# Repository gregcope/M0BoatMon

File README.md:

ABoatMon
========

A Moteino M0 (hence the M0) Boat Monitoring solution!

Intro
=====

A reimplementation, and extension of https://github.com/gregcope/piboatmon, as the original consumed too much power.  This is designed with the following goals;
* Be very, very low power
* Chargable from 12-24V 
* Has a rechargable LIPO battery

The present version is made from COTS parts to make life easy at the deign/proto stage.  However the code should be transferable.

Parts
=====
* [Adafruit Ultimate GPS](https://www.adafruit.com/product/746) - any 3.3v UART GPS would do, however needs an enable pin and vbat GPS almanac backup
* [Adafruit Fona](https://www.adafruit.com/product/1946) - any 3.3v UART GSM modem would do, although we do use the battery charging on the fona
* [Low power Moteino M0](https://lowpowerlab.com/shop/product/184) 
* [Mini Step Down Regulator Voltag Power Supply Module 4.5v~55v to 5v](https://www.ebay.co.uk/sch/i.html?_osacat=0&_odkw=Mini+Step+Down+Regulator+Voltag+Power+Supply+Module+4.5v~55v+to+5v&_from=R40&_trksid=p2334524.m570.l1313.TR0.TRC0.H0.XMini+Step+Down+Regulator+Voltag+Power+Supply+Module+4.5v~55v+to+5v+600ma.TRS0&_nkw=Mini+Step+Down+Regulator+Voltag+Power+Supply+Module+4.5v~55v+to+5v+600ma&_sacat=0).  Specifically the one with an enable pin and low power in off mode (<10ua).  Needs to supply 500ma+ (600ma is fine) and deal with 11-30v on the input to work on 12V or 24V systems.  Needs to supply 5V for the lipo charger.  Efficiency is not a massive issue as the regulator is off most of the time, only on to charge occassionally.
* [DS18B20 Waterproof Digital Probe Temperature Sensor with Silicone Cable (higher temp) Thermometer](https://www.ebay.co.uk/sch/i.html?_from=R40&_trksid=p2380057.m570.l1313.TR0.TRC0.H0.Xvermont+l+tent.TRS0&_nkw=DS18B20+Waterproof+Digital+Probe+Temperature+Sensor+Silicone+Cable+Thermometer&_sacat=0)
* [12V 12mm LED Power Push Button Switch Momentary Waterproof Metal 4 Pin](https://www.ebay.co.uk/sch/i.html?_osacat=0&_odkw=waterproof+LED+switch+12mm&_from=R40&_trksid=p2334524.m570.l1313.TR0.TRC0.H0.Xwaterproof+LED+switch+12mm+momentary.TRS0&_nkw=waterproof+LED+switch+12mm+momentary&_sacat=0)
* 1200mah LIPO Battery (any single cell LIPO with a JST would do)
* Bilge Switch (any normally closed, simple switch would do)

External Libs
=======

* [Tinygps++](https://github.com/mikalhart/TinyGPSPlus) - A class to deal with GPS
* [Lowpower](https://github.com/LowPowerLab/LowPower) - A class to help with Sleep modes
* Eeprom - Save Eeprom state
* [OneWire](https://github.com/PaulStoffregen/OneWire) - DS18B20 Temp sensor lib

Internal Classes
========
* Device - A base, or standlone class to control power to devices via a Digital pin
* Config - A class to provide a config object to store Eeprom state
* CRC8 - CRC checksum (for config saving)
* Sleep - Simple wrapper to LowPower sleep

High Level Logic
================

* Switches is on setup configures all the required parts
* Loop every 8 secs and checks;
* Bilge switch
* Every 4 mins checks the batteries
* and if above 13.7v (ie charging) enables the onboard lipo charger
* Reports bilge switch or low BatV
* Every Hour;
* Checkst the above
* Checks location
* If any of the above are out of band;
* Send a message

HowTo
=====

1. Open a command terminal, and change cd to where your Ardunio IDE stores code
```cd Documents/Arduino```
2. Clone the repo
```git clone https://github.com/gregcope/ABoatMon.git```
3. Open Ardunio IDE and open ```ABoatMon.ino```

http://arduino.stackexchange.com/questions/348/how-to-organize-my-arduino-projects-structure-for-easy-source-control

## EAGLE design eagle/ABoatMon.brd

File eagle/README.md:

# Eagle Files

0. Uses Sparkfun DRC file
1. ERC and DRC check clean
2. Top and bottom Copper Pour
3. Nets Classes use 24 mil width and 16mil clearance
4. Polygons use Isolate 12 mil
5. Layer 26 bNames - bottom silkscreen has board dimensions on it

## Design

0. I may add more parts...
1. Uses a MoteinoMega, Adafruit Ultimate GPS and an Adafruit FONA GSM
2. The P-channel Mosfet is designed to power the GPS directly, avoiding the on board regulator
3. The VBAT is on the MotinoMega 3.3V rail to keep the GPS backup circuits powered
4. The JST is for a Lipo battery
5. Their is a 1.8M/3.3M VCC voltage divider to monitor the LIPO, with a 0.1uF capacitor - see [Jeelabs post here](https://jeelabs.org/2013/05/16/measuring-the-battery-without-draining-it/)
6. Terminal Connector is for a simple Bilge switch for the Moteino to monitor
7. Terminal Connector for a Button
8. Terminal Connector for an LED
9. Terminal Connector for a DS18B20 Temp probe powered from a GPIO pin
10. Terminal Connector 12V-24V VCC input
11. A 27M/3.3M voltage divider to measure 30+V on an ADC pin
12. Headers for Fona GSM module
13. Terminal Connector for a 5v cable to connect to the Fona USB charge port
14. There is a jumper to measure the uCurrent the board uses from the LIPO, and also by-pass the switching (aka an on/off switch)
15. There is a jumper to measure the uCurrent the board uses from VCC, and also by-pass the switching (aka an on/off switch)
16. Voltage regulator uses a [holtek HT7463A](http://www.holtek.com/documents/10179/116711/HT7463A_Bv130.pdf)

... What's missing?

No thread is complete without pictures...

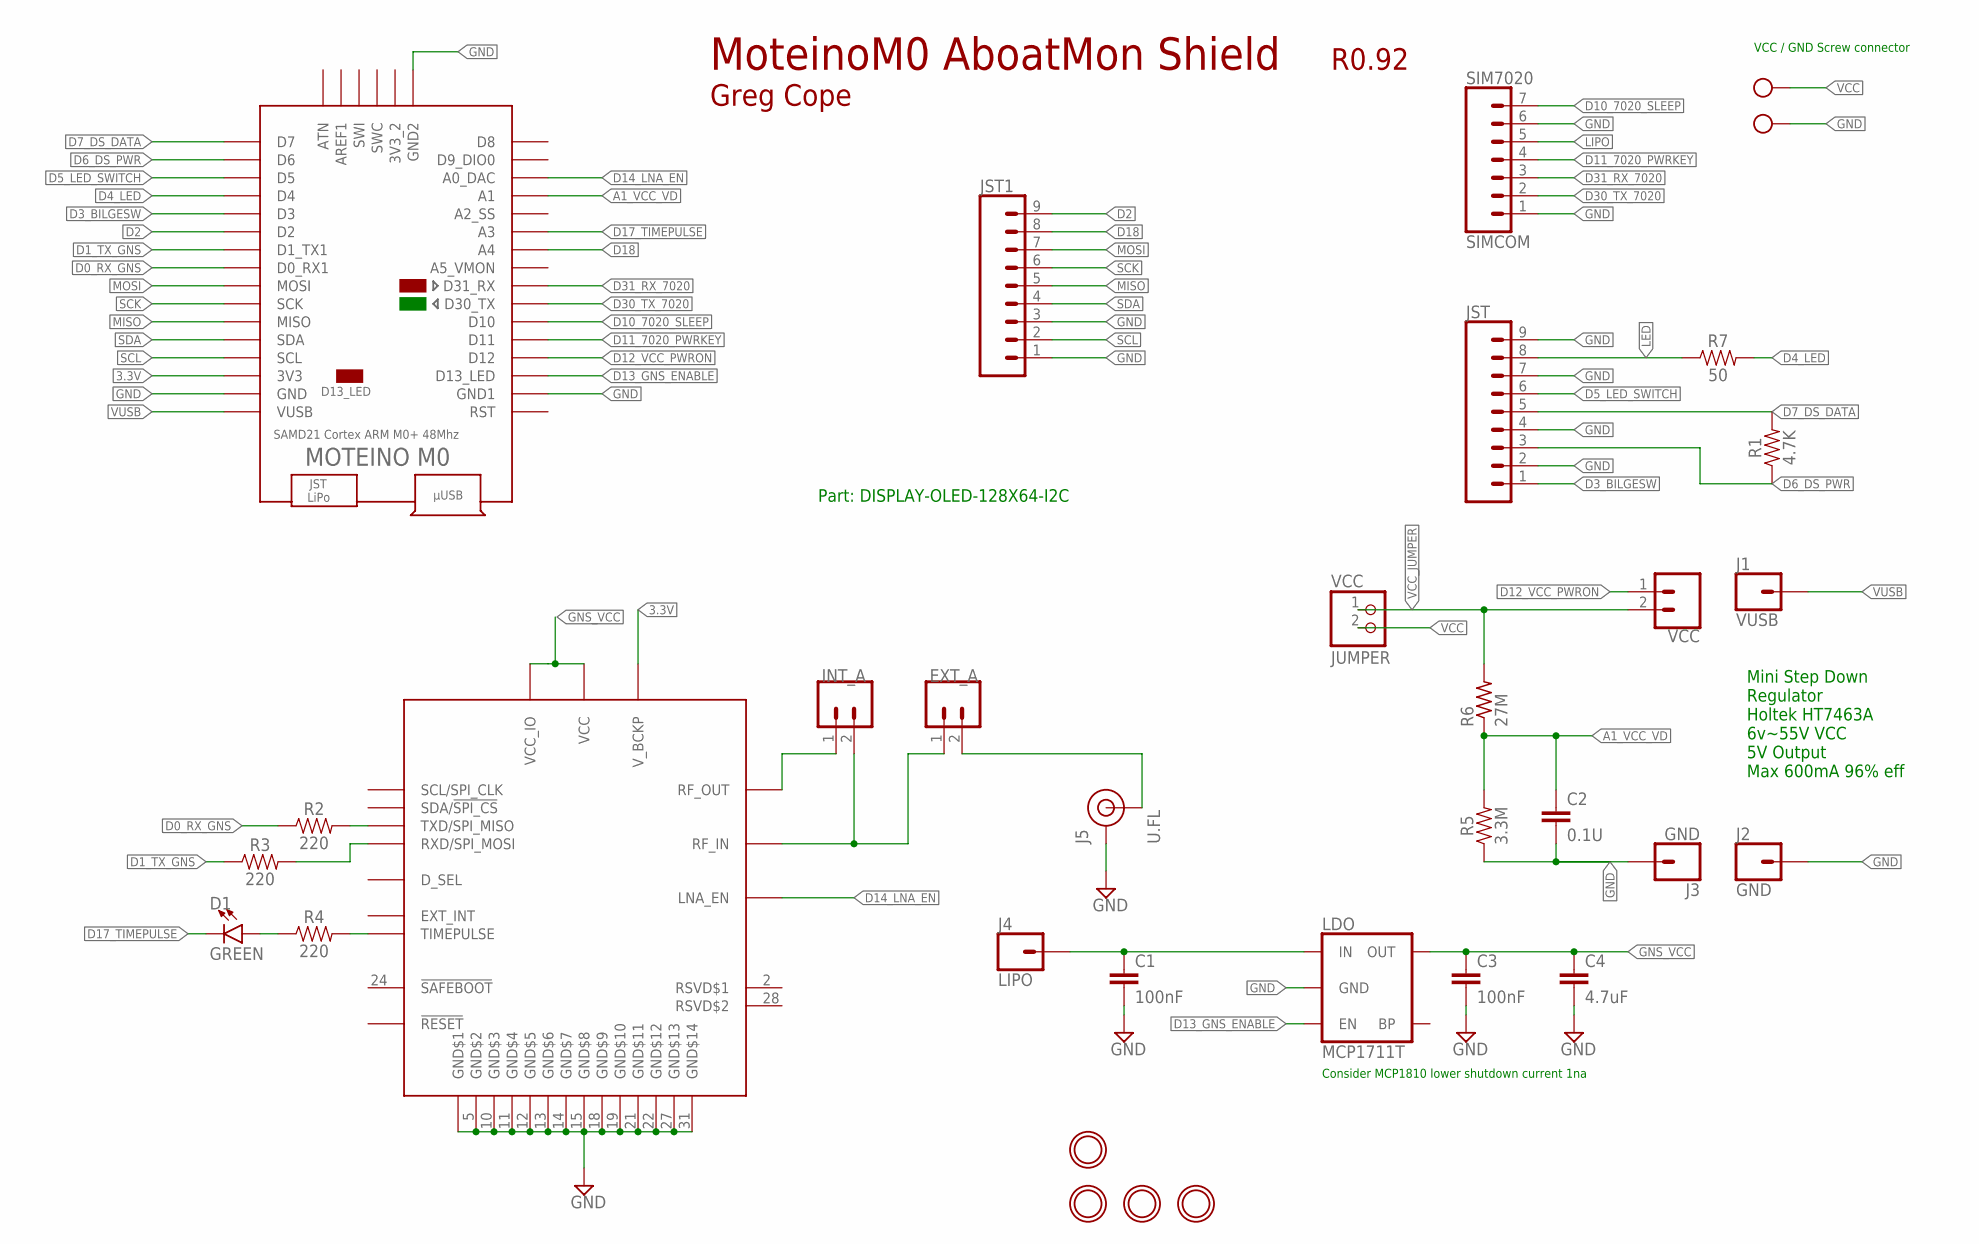
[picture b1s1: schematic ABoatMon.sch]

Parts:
C1, C3: 100nF; 0603
C2: 0.1U; CAP-PTH-SMALL-KIT
C4: 4.7uF; 0603
D1: GREEN; LED-0603
ENABLE: VCC; 1X02
EXT_A: CONN_02; 1X02
GND: MOUNTINGHOLE2.5; MOUNTINGHOLE_2.5_PLATED
INT_A: CONN_02; 1X02
J1: VUSB; 1X01
J2, J3: GND; 1X01
J4: LIPO; 1X01
J5: U.FL
JST, JST1: CONN_09; 1X09
LDO: MCP1711T; SOT23-5
R1: 4.7K; AXIAL-0.3
R2, R3, R4: 220; 0603
R5: 3.3M; AXIAL-0.3
R6: 27M; 0309/12
R7: 50; AXIAL-0.3
SIM7020: SIMCOM; 1X07
U$3, U$9: MOUNTINGHOLE2.0; MOUNTINGHOLE_2.0_PLATED
U$5: CAM-M8
U$6: MOTEINO_M0
U$7: MOUNTINGHOLE2.5; MOUNTINGHOLE_2.5_PLATED
VCC: JUMPER; 1X02_ROUND
X1: MKDSN1,5/2-5,08

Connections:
3.3V: U$5.8 (V_BCKP), U$6.3V3
A1_VCC_VD: C2.1, R5.P$2 (2), R6.1, U$6.A1
D0_RX_GNS: R2.1, U$6.D0_RX1
D1_TX_GNS: R3.1, U$6.D1_TX1
D2: JST1.9, U$6.D2
D3_BILGESW: JST.1, U$6.D3
D4_LED: R7.P$2 (2), U$6.D4
D5_LED_SWITCH: JST.6, U$6.D5
D6_DS_PWR: JST.3, R1.P$1 (1), U$6.D6
D7_DS_DATA: JST.5, R1.P$2 (2), U$6.D7
D10_7020_SLEEP: SIM7020.7, U$6.D10
D11_7020_PWRKEY: SIM7020.4, U$6.D11
D12_VCC_PWRON: ENABLE.1, U$6.D12
D13_GNS_ENABLE: LDO.3 (EN), U$6.D13 (D13_LED)
D14_LNA_EN: U$5.30 (LNA_EN), U$6.A0_DAC
D17_TIMEPULSE: D1.C, U$6.A3
D18: JST1.8, U$6.A4
D30_TX_7020: SIM7020.2, U$6.D30_TX
D31_RX_7020: SIM7020.3, U$6.D31_RX
GND: C1.2, C2.2, C3.2, C4.2, J2.1, J3.1, J5.1 (GND), J5.2 (GND), JST.2, JST.4, JST.7, JST.9, JST1.1, JST1.3, LDO.2 (GND), R5.P$1 (1), SIM7020.1, SIM7020.6, U$5.4 (GND$1), U$5.5 (GND$2), U$5.10 (GND$3), U$5.11 (GND$4), U$5.12 (GND$5), U$5.13 (GND$6), U$5.14 (GND$7), U$5.15 (GND$8), U$5.18 (GND$9), U$5.19 (GND$10), U$5.21 (GND$11), U$5.22 (GND$12), U$5.27 (GND$13), U$5.31 (GND$14), U$6.GND, U$6.GND_1 (GND1), U$6.GND_2 (GND2), X1.2
GNS_VCC: C3.1, C4.1, LDO.5 (OUT), U$5.1 (VCC_IO), U$5.9 (VCC)
LED: JST.8, R7.P$1 (1)
LIPO: C1.1, J4.1, LDO.1 (IN), SIM7020.5
MISO: JST1.5, U$6.MISO
MOSI: JST1.7, U$6.MOSI
unnamed: R4.2, U$5.29 (TIMEPULSE)
unnamed: R2.2, U$5.25 (TXD/SPI_MISO)
unnamed: R3.2, U$5.26 (RXD/SPI_MOSI)
unnamed: D1.A, R4.1
unnamed: EXT_A.1, INT_A.2, U$5.17 (RF_IN)
unnamed: EXT_A.2, J5.FEED (SIGNAL)
unnamed: INT_A.1, U$5.16 (RF_OUT)
SCK: JST1.6, U$6.SCK
SCL: JST1.2, U$6.SCL
SDA: JST1.4, U$6.SDA
VCC: VCC.2, X1.1
VCC_JUMPER: ENABLE.2, R6.2, VCC.1
VUSB: J1.1, U$6.VUSB

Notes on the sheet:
Mini Step Down Regulator Holtek HT7463A 6v~55V VCC 5V Output Max 600mA 96% eff
Greg Cope
R0.92
MoteinoM0 AboatMon Shield
Consider MCP1810 lower shutdown current 1na
VCC / GND Screw connector
Part: DISPLAY-OLED-128X64-I2C

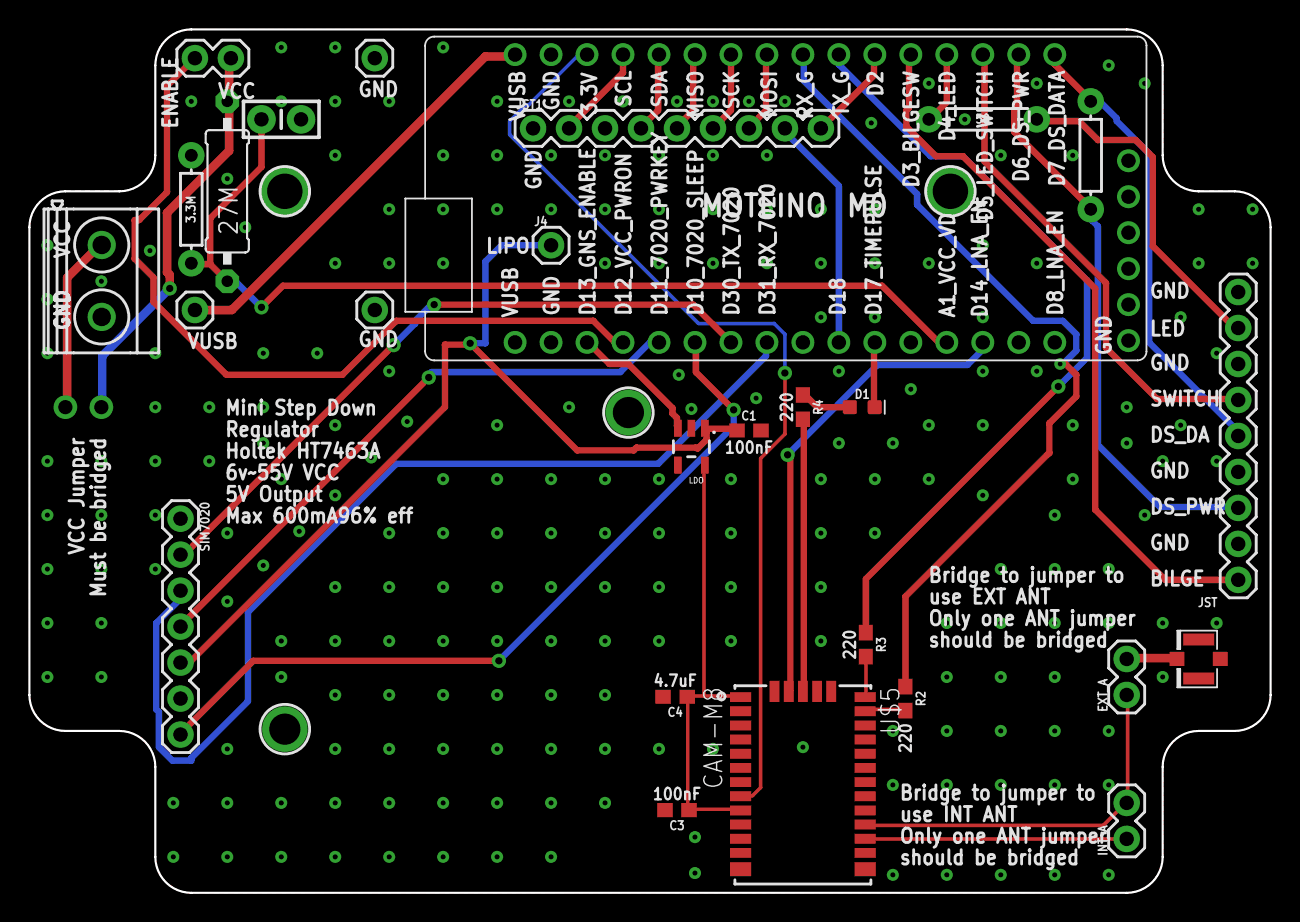
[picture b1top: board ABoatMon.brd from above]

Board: 2 copper layers, 87.6 x 61.0 mm, 32 parts (0 on the bottom side), 38 nets.

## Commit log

2019-01-03 added M0
2019-01-03 readme update
2019-10-27 added CAM-M8
2019-10-27 started adding nets
2019-10-28 moved M0 and regulator
2019-10-28 changed nets for gns
2019-10-29 first pass with vias - one airwire
2019-10-31 added tab
2019-11-01 added u.ft, moved GNS
2019-11-04 errors cleared
2019-11-04 DRC errors oshpark DRU fixed
2019-11-04 First pass at 7020 mount holes
2019-11-04 Silkscren fixes
2019-11-06 added GND vias
2019-11-09 ABoatMon_2019-11-07.zip R2 sent to fab
2019-11-20 Started R0.9 1. Mounting hole wrong place 2. Regulator board needs to move down due to overlapping edge of casterlated holes 3. Mobile module needs to move right 1mm due to sharp lower left edge hitt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
2019-11-20 Mounting hole and ufl moved
2019-11-20 pushed out tab sizes on either end
2019-11-20 fixed a radius to 100
2019-11-20 rebased, 100 radius fixed, added GND vias
2019-11-20 removed wires
2019-11-20 routed
2019-11-20 Moved LIPO label, all fixes done
2019-11-20 Readme updates
2019-11-23 D7000 wrong way round, moved 10pin jst
2019-11-23 Moved power jumper, added jumper txt
2019-11-23 Clearance DRC errors fixed
2019-11-24 DRC, ERC checked. Moved routes away from GNS chip
2019-11-24 removed a wire stub
2019-11-24 removed too many wire stubs. DRC and ERC pass now
2019-11-25 added a via, move a trace
2019-11-25 added zip
2019-12-08 Moved JSTs
2019-12-08 Moved SIM7000 up a bit

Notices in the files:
parts and their libraries:
SparkFun-Capacitors: Licensing: Creative Commons ShareAlike 4.0 International - https://creativecommons.org/licenses/by-sa/4.0
